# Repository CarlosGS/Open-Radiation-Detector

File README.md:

# Open Radiation Detector
Portable radiation detector based on a ionization chamber.

The KiCad PCB sources and BOM can be found in the repository's subfolders.

Check out <https://hackaday.io/project/27508-open-radiation-detector> for more information.

# Next version:

# The detector works!

Progress
--
- October 2017: Designed, build and document a prototype to participate in the Hackaday Prize.

- 5/May/2017: The radiation sensor concept has been incorporated into a connected sensor board. It looks like the effect of nearby electrostatic fields still affects the voltage output, regardless of the back plane being connected to either guard voltage or ground (maybe this is due to the large size of the electrode?). The board uses the PNP configuration polarized with 10 MOhm 1% and an op-amp driver (LM2904DR) to minimize the effect of ADC current consumption. It includes a duplicate circuit unconnected from the electrode, to be used as a compensation for temperature effects.

- 15/Feb/2017: It works! At first the result with the new transistors had lots of noise as well. But adding a copper plane behind the main electrode seems to have done the trick. So maybe the transistors were not the problem after all! The pictures show a new prototype being tested with and without a radiation source. Its response ranges from 70mV to 160mV and it is way more stable than before. Schematic is [Charles Wenzel's Experimenters Ionization Chamber](http://www.techlib.com/science/ion.html#Experimenters%20Chamber) with an FMMT634TA NPN darlington transistor.

- 8/Feb/2017: The Darlington transistors used until now (MMBT6427, MMBTA14, MMBTA28, MMBTA63, MMBTA64) may not be suitable for detecting the low currents involved in this detection problem (nA or even pA). Yet again I have resorted to Charles Wenzel's awesome website. A proper surface-mount alternative to the MPSAW45A power darlington transistor may be the FMMT634 and FMMT734. So I've ordered a bunch of these transistors in order to test the concept again.

- Week of 7/Feb/2017: The new approach is to use an actual ion chamber that uses a copper electrode insulated from ground by an outer guard ring. The chamber itself is made of [a standard size, commercially available PCB shielding can](http://www.mouser.es/Search/ProductDetail.aspx?R=BMI-S-104virtualkey64820000virtualkey739-BMI-S-104) (in the pictures you can see my attempt at creating one with tin sheet from a metal can). The first prototype actually seemed to have some reaction during the tests. However the second prototype did not. [G-code to mill the electrode](http://jscut.org/jscut.html?gist=c962737e35c9f9b0445b82d079ceb10d).

- On a second thought, the "finger electrodes" may not be a good idea. Since there is a large contact area between each finger, there surely is a lot of leakage current that will mask-out any ion-induced current (one of the biggest concerns explained by [Charles Wenzel's ion chamber website](http://www.techlib.com/science/ion.html))

- 19/Jan/2017 Finally got a .9uCi AM241 source to test, it will be the benchmark for the detector. Unfortunately, the first attempts with the amplifier circuit yield very noisy measurements, that mainly depend on wind and humidity. Surprisingly (to me), it is also very dependent on static electricity. I've also tested again the spark particle detector, but there seems to be absolutely no relation between the sparks and the proximity of the radiation source. Maybe the finger electrodes are too "pointy" because of the manufacture method (milling)? [pic1](pictures/fingerElectrodeZoom1_19Jan2017.jpg) [pic2](pictures/fingerElectrodeZoom2_19Jan2017.jpg)

- Week of 9/Jan/2017: Simulation of circuit amplifiers ["click type"](http://lushprojects.com/circuitjs/circuitjs.html?cct=$+1+0.000015625+31.41906602856942+68+5+50%0Ag+928+416+928+464+0%0A177+928+224+912+352+0+0.7312725129613747+0.7310030522124785+0.000049999999999999996+0.002+12%0Ac+800+320+800+384+0+0.000022000000000000003+0.7321707154576954%0Ag+800+384+800+432+0%0Ar+800+320+736+320+0+8200%0Ar+800+320+896+320+0+33000%0A211+928+352+976+304+0+1+8000+1%0Ar+928+416+928+352+0+40%0Aw+800+320+928+224+0%0Ac+880+112+880+160+0+0.000022000000000000003+6.122038321055448%0AR+880+112+832+80+0+0+40+8.4+0+0+0.5%0Ar+944+112+944+160+0+33000%0Aw+880+112+944+112+0%0Aw+880+160+944+160+0%0A162+944+160+928+224+1+2.1+1+0+0+0.01%0Aw+688+288+688+160+0%0Aw+640+160+688+160+0%0Aw+640+192+640+160+0%0Ar+272+304+336+208+0+1000000000%0Ar+640+224+640+304+0+18%0Aw+624+448+688+448+0%0Aw+736+320+688+320+0%0Ar+688+320+688+448+0+220.00000000000003%0Aw+304+336+336+448+0%0Aw+624+448+336+448+0%0Aw+592+208+336+208+0%0A174+272+368+304+304+0+200000000000+0.9851000000000001+Resistance%0Ag+624+448+624+480+0%0At+640+304+688+304+0+1+-0.1533803623127099+0.664742220730739+20000%0At+592+208+640+208+0+-1+-0.263860697764259+-0.4172092930979039+20000%0Aw+688+160+880+112+0%0Ao+7+64+0+2337+0.5846006549323611+0.023384026197294447+0+-1+0%0Ao+14+64+0+2337+1.25+0.0015625+1+-1+0%0Ao+4+1024+0+2337+5+0.0015625+2+-1+0%0Ao+21+64+0+2338+10+0.00078125+3+-1+0%0A), ["LED scale type"](http://lushprojects.com/circuitjs/circuitjs.html?cct=$+1+0.000015625+31.41906602856942+68+5+50%0Ar+784+320+784+464+0+167%0AR+432+96+384+64+0+0+40+12+0+0+0.5%0A162+720+336+720+400+1+2.35+1+0+0+0.02%0Aw+496+176+496+96+0%0Aw+432+96+496+96+0%0Aw+432+128+432+96+0%0Aw+96+272+128+384+0%0Aw+288+384+128+384+0%0Aw+384+144+128+144+0%0A174+64+304+96+240+0+100000000000+0.49010000000000004+Resistance%0Ag+432+384+432+416+0%0At+464+192+496+192+0+1+-6.516184439164558+0.5942797072286803+20000%0At+384+144+432+144+0+-1+6.075435564035981+-0.44074887512857686+20000%0Ar+432+384+288+384+0+1000%0A162+592+208+592+272+1+2.4+0+1+0+0.02%0A162+656+272+656+336+1+2.35+1+1+0+0.02%0Ag+656+464+656+496+0%0Aw+592+464+656+464+0%0Aw+592+208+784+208+0%0Ar+592+464+592+272+0+2700%0Ar+720+464+720+400+0+470%0Ar+656+464+656+336+0+1800%0Aw+592+208+496+208+0%0Aw+656+464+720+464+0%0Aw+720+464+784+464+0%0Aw+592+272+656+272+0%0Aw+656+336+720+336+0%0Aw+432+160+464+192+0%0Az+784+320+784+208+1+0.805904783+5%0A174+432+240+464+304+0+10000000+0.12380000000000002+Resistance%0Aw+432+240+432+160+0%0Aw+432+384+432+304+0%0Aw+432+304+464+272+0%0Aw+64+240+128+144+0%0Ao+22+64+0+2338+20+0.05+0+-1+0%0Ao+0+64+0+2337+5+0.05+1+-1+0%0A)

- Self-ask the question: How to make a simple low-cost radiation detector? Begin to learn about ionization chambers thanks to [Charles Wenzel's website](http://www.techlib.com/science/ion.html).

- Week of 1/Jan/2017: First learn of spark particle detectors. [Design, build and test a PCB electrode](https://github.com/vlachoudis/bCNC/pull/480) (but without any radiation source to be tested). [video](https://www.youtube.com/watch?v=s3N2EDGwe9U)

# License
This work is licensed under a Creative Commons Attribution 4.0 International License.
<https://creativecommons.org/licenses/by/4.0/>

Please cite as:
--
Garcia-Saura, C. (2017). Open Radiation Detector. GitHub. https://doi.org/10.5281/ZENODO.10446305

Latex / Bibtex citation:
```bibtex
@misc{garciasaura2017rad,
  author = {Garcia-Saura, Carlos},
  title = {Open Radiation Detector},
  publisher = {GitHub},
  year = {2017},
  doi = {10.5281/ZENODO.10446305},
  url = {https://doi.org/10.5281/ZENODO.10446305}
}
```

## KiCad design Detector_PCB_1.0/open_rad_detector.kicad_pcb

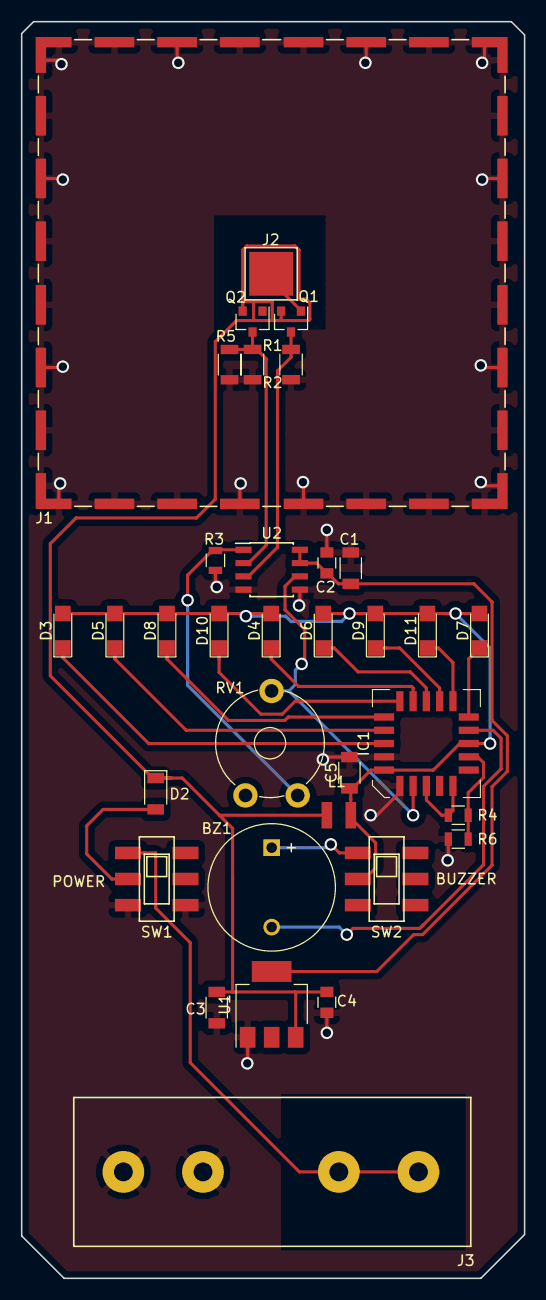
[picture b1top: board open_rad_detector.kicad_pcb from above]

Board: 2 copper layers, 48.1 x 120.3 mm, 34 parts (0 on the bottom side), 24 nets.

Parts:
BZ1: Buzzer; MagneticBuzzer_ProSignal_ABI-010-RC
C1, C3, C5: 10u; C_1206
C2, C4: 100n; C_0805
D2: D; D_1206
D3, D4, D5, D6, D7, D8, D9, D10, D11: LED; LED_1206
IC1: LM3914V; PLCC-20
J1: Outer_Shield; Laird_Technologies_BMI-S-107_44.37x44.37mm
J2: Electrode; 1Pin
J3: Batt; A23_battery
L1: 33u; Neosid_Inductor_SM-NE29_SMD1008
Q1, Q2: FMMT734; SOT-23
R1, R2: 10M; R_1206
R3: R_G; R_0805
R4: LMR1; R_0805
R5: Rtune; R_1206
R6: LMR2; R_0805
RV1: R_F; Potentiometer_Trimmer_Piher_PT-10v10_Horizontal_Px10.0mm_Py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
SW1: POWER; SW_JS202011SCQN
SW2: BUZZER; SW_JS202011SCQN
U1: LD1117S50TR_SOT223; SOT-223-3_TabPin2
U2: MCP6N11; SOIC-8_3.9x4.9mm_Pitch1.27mm

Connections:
+5V: C1.1, C2.1, U1.2, U2.7, U2.8
+12V: C5.1, D3.2, D4.2, D5.2, D6.2, D7.2, D8.2, D9.2, D10.2, D11.2, IC1.3, IC1.11, L1.2, SW2.2
+BATT: C3.1, C4.1, D2.1, L1.1, Q1.2, Q2.2, U1.3
GND: C1.2, C2.2, C3.2, C4.2, C5.2, IC1.2, IC1.4, J1.1, J3.1, R1.2, R2.2, R3.2, R5.2, R6.2, SW1.3, U1.1, U2.4, U2.5
L1: D3.1, IC1.1
L2: D5.1, IC1.20
L3: D8.1, IC1.19
L4: D10.1, IC1.18
L5: D4.1, IC1.17
L6: D6.1, IC1.16
L7: D9.1, IC1.15
L8: D11.1, IC1.14
L9: D7.1, IC1.13
L10: BZ1.2, IC1.12
unnamed: BZ1.1, SW2.1
unnamed: D2.2, SW1.2
unnamed: IC1.6, IC1.8, R4.1
unnamed: IC1.10, R4.2, R6.1
unnamed: J2.1, Q1.1
unnamed: J3.2, SW1.1
v_comp: Q2.3, R1.1, R5.1, U2.2
v_fg: R3.1, RV1.1, U2.1
v_out: IC1.5, RV1.2, U2.6
v_rad: Q1.3, R2.1, U2.3

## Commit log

2017-10-17 Released version 0.9 of the detector
2017-10-17 Added BOM
2017-10-17 New version. Work in progress.
2017-10-17 Adapted to latest version of KiCad
2017-10-17 Added LEDs
2017-10-18 Work in the new version
2017-10-18 Moved pictures
2017-10-18 Support latest KiCad version
2017-10-21 Added BOM and Gerbers for V1.0
2023-12-31 Included DOI and Bibtex citation references

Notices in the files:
Detector_PCB_1.0/open_rad_detector.kicad_pcb:
License: Creative Commons Attribution-ShareAlike 4.0 International​
